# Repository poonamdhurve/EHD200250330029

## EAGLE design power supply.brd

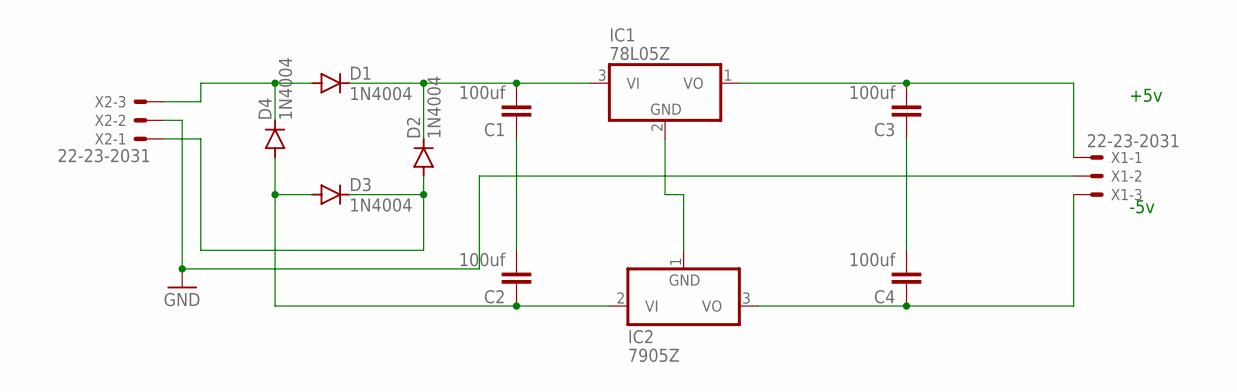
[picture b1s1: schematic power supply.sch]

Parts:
C1, C2, C3, C4: 100uf; C2.5-3
D1, D2, D3, D4: 1N4004; DO41-10
IC1: 78L05Z; TO92
IC2: 7905Z; TO92
X1, X2: 22-23-2031

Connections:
GND: X1.2, X2.2
unnamed: D1.A, D4.C, X2.3
unnamed: C2.1, D3.A, D4.A, IC2.2 (VI)
unnamed: D2.A, D3.C, X2.1
unnamed: C1.2, D1.C, D2.C, IC1.3 (VI)
unnamed: IC1.2 (GND), IC2.1 (GND)
unnamed: C1.1, C2.2
unnamed: C4.1, IC2.3 (VO), X1.3
unnamed: C3.2, IC1.1 (VO), X1.1
unnamed: C3.1, C4.2

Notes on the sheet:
+5v
-5v

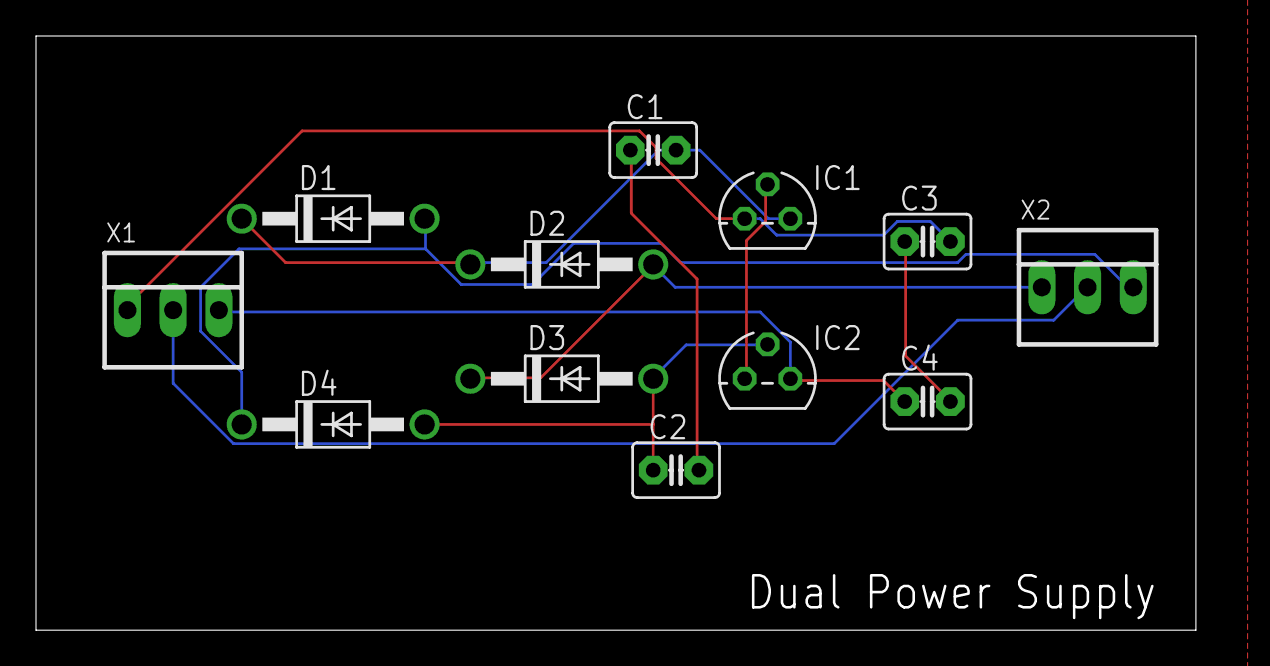
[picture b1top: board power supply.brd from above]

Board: 2 copper layers, 66.6 x 33.0 mm, 12 parts (0 on the bottom side), 10 nets.

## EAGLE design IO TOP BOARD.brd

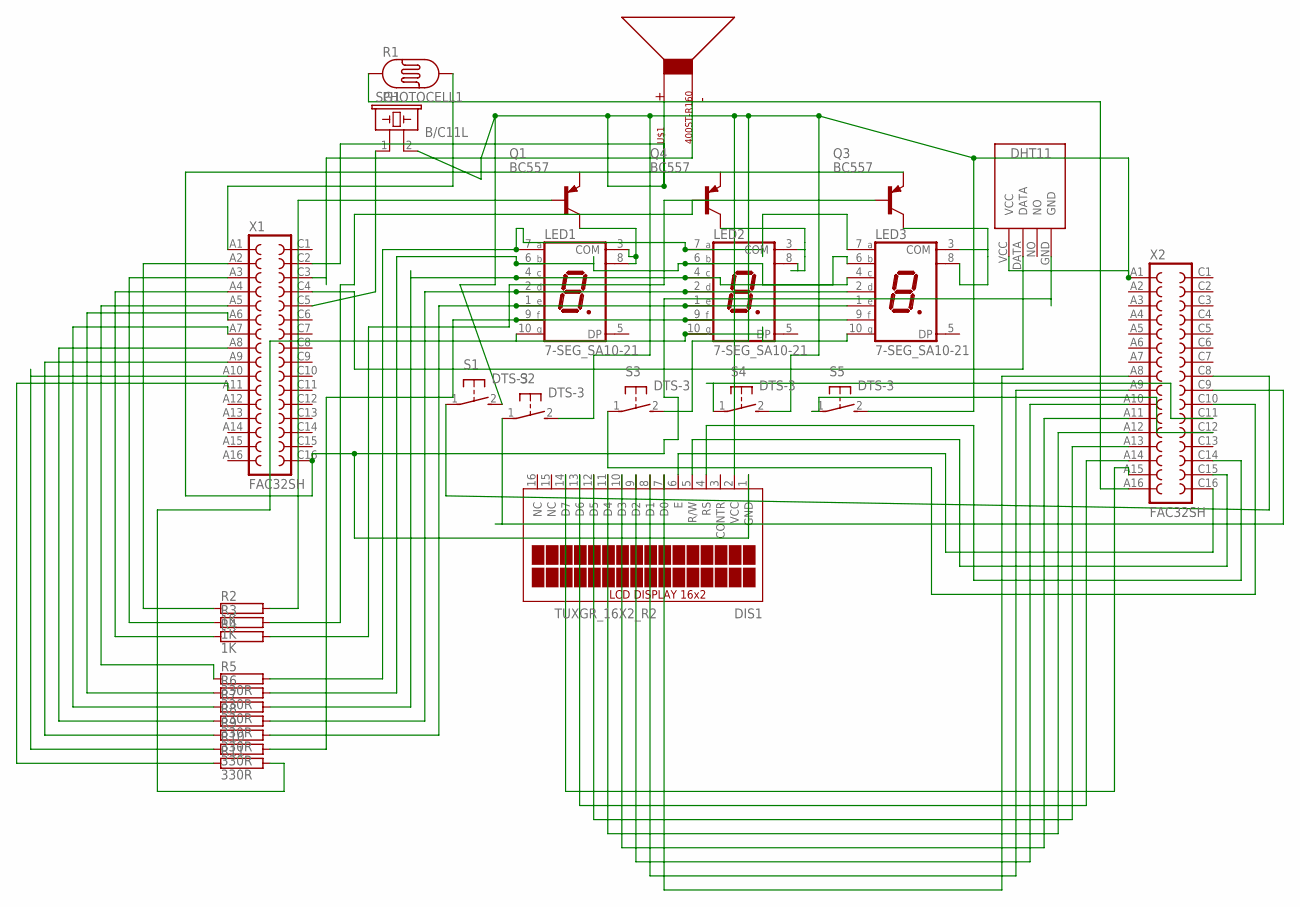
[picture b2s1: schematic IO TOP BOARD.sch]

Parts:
DIS1: TUXGR_16X2_R2
LED1, LED2, LED3: 7-SEG_SA10-21; SA10-21
Q1, Q3, Q4: BC557; TO92
R1: PHOTOCELL1; LDR_OFFBOARD
R2, R3, R4: 1K; TO-247-2H
R5, R6, R7, R8, R9, R10, R11: 330R; TO-247-2H
S1, S2, S3, S4, S5: DTS-3
SG1: B/C11L
U$1: 400ST-R160; 400STR160
U$2: DHT11
X1, X2: FAC32SH

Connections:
unnamed: LED1.3 (COM), LED1.8 (COM), Q1.3 (C)
unnamed: U$1.P$2, X1.C3
unnamed: U$2.DATA, X1.C4
unnamed: SG1.1, X1.C5
unnamed: DIS1.6 (E), X2.C16
unnamed: DIS1.5 (R/W), X2.C15
unnamed: DIS1.4 (RS), X2.C14
unnamed: R1.1, X2.A16
unnamed: DIS1.7 (D0), X2.A8
unnamed: DIS1.8 (D1), X2.A9
unnamed: DIS1.9 (D2), X2.A10
unnamed: DIS1.10 (D3), X2.A11
unnamed: DIS1.11 (D4), X2.A12
unnamed: DIS1.12 (D5), X2.A13
unnamed: DIS1.13 (D6), X2.A14
unnamed: DIS1.14 (D7), X2.A15
unnamed: S1.1, X2.C8
unnamed: S2.1, X2.C9
unnamed: S3.1, X2.C10
unnamed: S4.1, X2.C11
unnamed: S5.1, X2.C12
unnamed: DIS1.2 (VCC), S1.2, S2.2, S3.2, S4.2, S5.2, SG1.2, U$1.P$1, U$2.VCC, X1.C2, X2.A1
unnamed: DIS1.1 (GND), Q3.1 (E), U$2.GND, X1.C16
unnamed: R1.2, X1.A1
unnamed: LED2.3 (COM), LED2.8 (COM), Q4.3 (C)
unnamed: LED3.3 (COM), LED3.8 (COM), Q3.3 (C)
unnamed: Q1.2 (B), R2.2
unnamed: Q4.2 (B), R3.2
unnamed: Q3.2 (B), R4.2
unnamed: LED1.7 (A), LED2.7 (A), LED3.7 (A), R5.2
unnamed: LED1.6 (B), LED2.6 (B), LED3.6 (B), R6.2
unnamed: LED1.4 (C), LED2.4 (C), LED3.4 (C), R7.2
unnamed: LED1.2 (D), LED2.2 (D), LED3.2 (D), R8.2
unnamed: LED1.1 (E), LED2.1 (E), LED3.1 (E), R9.2
unnamed: LED1.9 (F), LED2.9 (F), LED3.9 (F), R10.2
unnamed: R5.1, X1.A5
unnamed: R2.1, X1.A2
unnamed: R3.1, X1.A3
unnamed: R4.1, X1.A4
unnamed: LED1.10 (G), LED2.10 (G), LED3.10 (G), R11.2
unnamed: R6.1, X1.A6
unnamed: R7.1, X1.A7
unnamed: R8.1, X1.A8
unnamed: R9.1, X1.A9
unnamed: R10.1, X1.A10
unnamed: R11.1, X1.A11

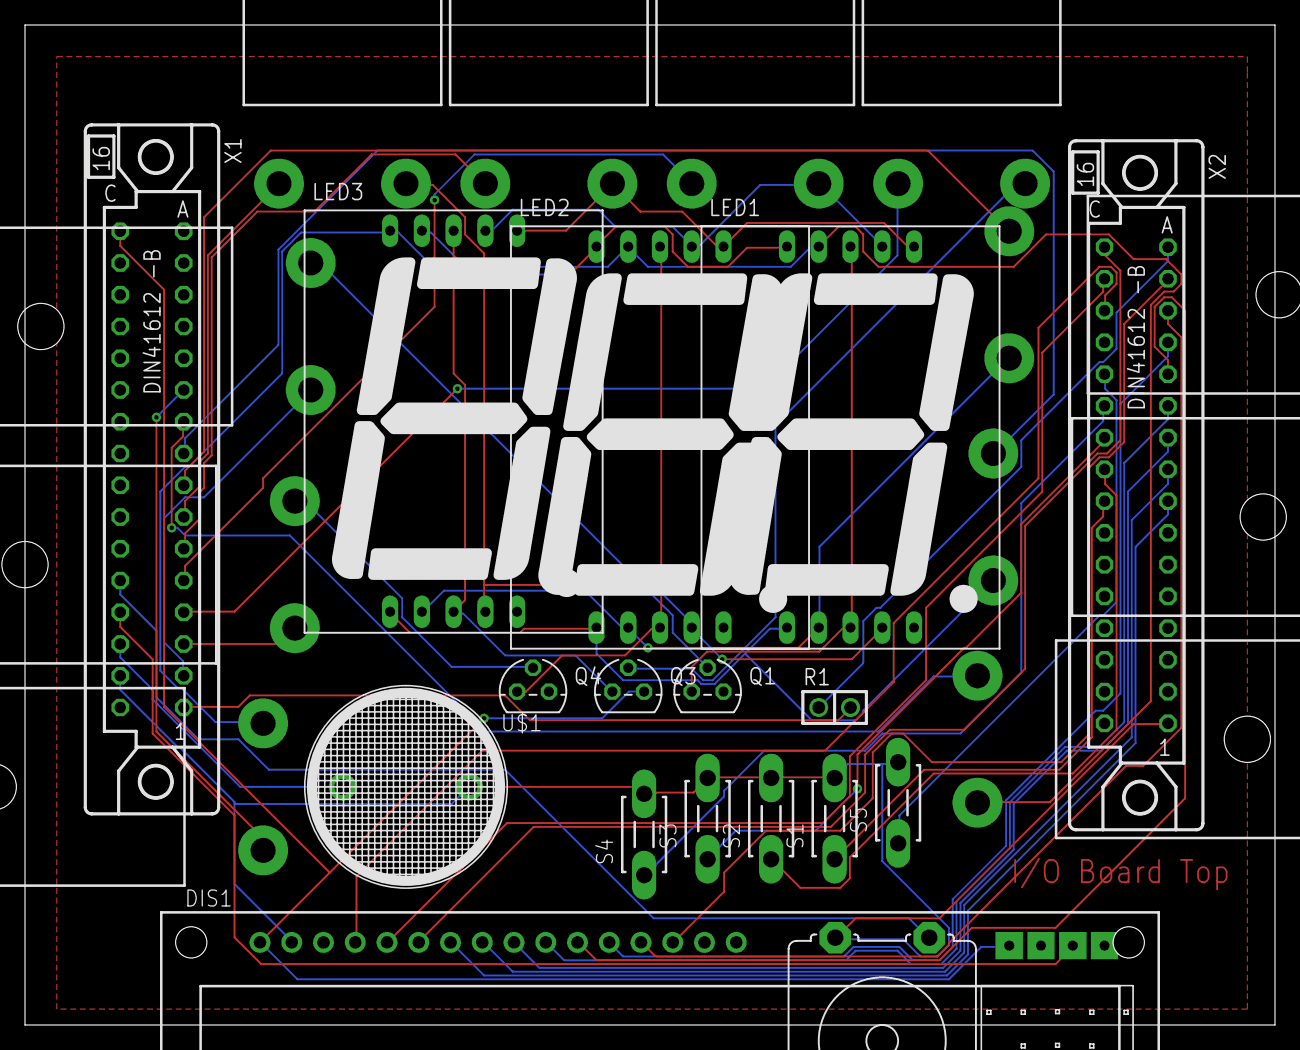
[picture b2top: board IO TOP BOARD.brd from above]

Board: 2 copper layers, 100.0 x 80.0 mm, 28 parts (0 on the bottom side), 46 nets.

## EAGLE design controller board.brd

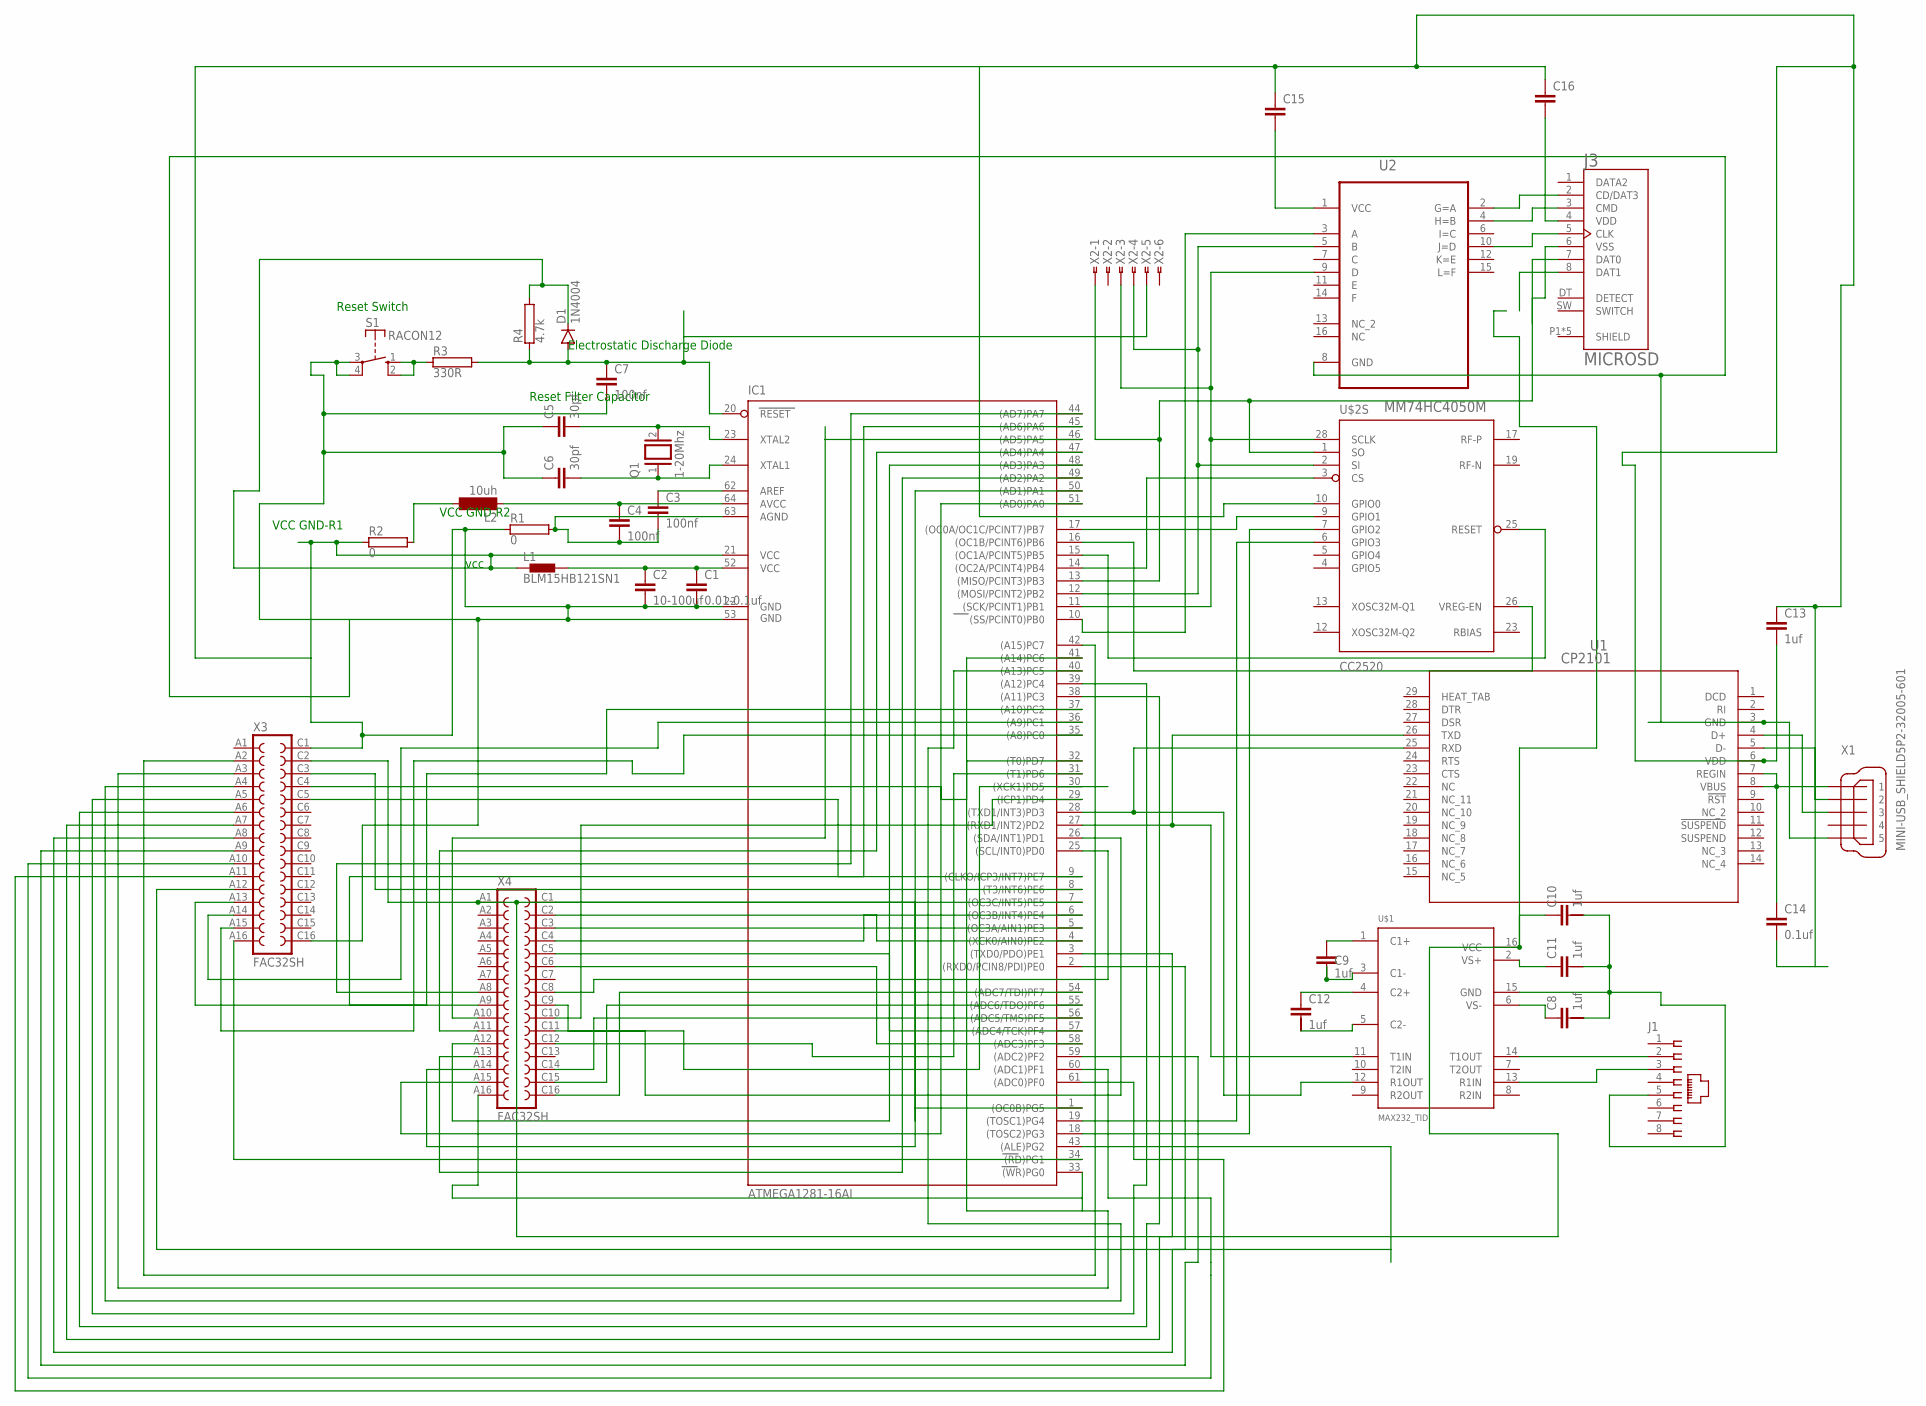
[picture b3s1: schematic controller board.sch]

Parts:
C1: 0.01-0.1uf; C2.5-3
C2: 10-100uf; C2.5-3
C3, C4, C7: 100nf; C2.5-3
C5, C6: 30pf; C2.5-3
C8, C9, C10, C11, C12: 1uf; C2.5/5-2
C13: 1uf; C2.5-3
C14: 0.1uf; C2.5-3
C15, C16: C2,5-3; C2.5-3
D1: 1N4004; DO41-10
IC1: ATMEGA1281-16AI; TQFP64
J1: 555248-1
J3: MICROSD; MOLEX_503182-1852
L1: BLM15HB121SN1; 0402
L2: 10uh; BS11
Q1: 1-20Mhz; Q
R1, R2: 0; TO-247-2H
R3: 330R; TO-247-2H
R4: 4.7k; TO-247-2H
S1: RACON12
U1: CP2101; MLP28_SIL
U2: MM74HC4050M; SOIC127P600X175-16N
U$1: MAX232_TID; R-PDSO-G16
U$2: CC2520; QFN50P500X500X100-29N
X1: MINI-USB_SHIELD5P2-32005-601; 32005-601
X2: FSIDE-6
X3, X4: FAC32SH

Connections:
AGND: U$2.29 (AGND)
AVDD: U$2.11 (AVDD), U$2.14 (AVDD), U$2.16 (AVDD), U$2.20 (AVDD), U$2.22 (AVDD)
AVDD-GUARD: U$2.24 (AVDD-GUARD)
DCOUPL: U$2.27 (DCOUPL)
DVDD: U$2.8 (DVDD)
unnamed: C1.1, C2.1, IC1.52 (VCC1), L1.2
unnamed: C5.2, IC1.23 (XTAL2), Q1.2
unnamed: C3.1, IC1.62 (AREF)
unnamed: C4.1, IC1.64 (AVCC), L2.1
unnamed: C3.2, C4.2, IC1.63 (AGND), R1.2
unnamed: L2.2, R2.2
unnamed: C9.2, C9.3, U$1.3 (C1-)
unnamed: C6.2, IC1.24 (XTAL1), Q1.1
unnamed: R3.1, S1.1 (S), S1.2 (S)
unnamed: C7.1, D1.A, IC1.20 (RESET), R3.2, R4.1, X2.5
unnamed: IC1.34 ((RD)PG1), X3.A16
unnamed: C9.1, U$1.1 (C1+)
unnamed: C12.1, U$1.4 (C2+)
unnamed: C12.2, U$1.5 (C2-)
unnamed: C11.1, U$1.2 (VS+)
unnamed: C8.1, U$1.6 (VS-)
unnamed: C8.2, C10.2, C11.2, J1.5, U$1.15 (GND)
unnamed: IC1.28 ((TXD1/INT3)PD3), U1.25 (RXD), U$1.12 (R1OUT)
unnamed: IC1.27 ((RXD1/INT2)PD2), U1.26 (TXD), U$1.11 (T1IN)
unnamed: U1.4 (D+), X1.3
unnamed: U1.5 (D-), X1.2
unnamed: C14.1, U1.7 (REGIN), U1.8 (VBUS), X1.1
unnamed: C1.2, C2.2, C5.1, C6.1, C7.2, C13.1, C13.2, C14.2, C15.1, C16.1, D1.C, IC1.21 (VCC), IC1.22 (GND), IC1.53 (GND1), L1.1, R1.1, R2.1, R4.2, S1.3, S1.4, U1.3 (GND), U1.6 (VDD), U2.8 (GND), U$2.10 (GPIO0), X1.5, X3.C1, X3.C16
unnamed: J1.2, U$1.14 (T1OUT)
unnamed: J1.3, U$1.13 (R1IN)
unnamed: IC1.18 ((TOSC2)PG3), U$2.7 (GPIO2)
unnamed: IC1.19 ((TOSC1)PG4), U$2.6 (GPIO3)
unnamed: IC1.11 ((SCK/PCINT1)PB1), U2.9 (D), U$2.28 (SCLK), X2.3
unnamed: C15.2, U2.1 (VCC)
unnamed: IC1.10 ((SS/PCINT0)PB0), U2.3 (A)
unnamed: IC1.12 ((MOSI/PCINT2)PB2), U2.5 (B), U$2.2 (SI), X2.4
unnamed: J3.2 (CD/DAT3), U2.2 (G=A)
unnamed: J3.3 (CMD), U2.4 (H=B)
unnamed: J3.5 (CLK), U2.10 (J=D)
unnamed: IC1.13 ((MISO/PCINT3)PB3), J3.7 (DAT0), U$2.1 (SO), X2.1
unnamed: IC1.15 ((OC1A/PCINT5)PB5), U$2.25 (RESET)
unnamed: C16.2, J3.4 (VDD)
unnamed: IC1.16 ((OC1B/PCINT6)PB6), U$2.26 (VREG-EN)
unnamed: IC1.14 ((OC2A/PCINT4)PB4), U$2.3 (CS)
unnamed: IC1.17 ((OC0A/OC1C/PCINT7)PB7), U$2.9 (GPIO1)
unnamed: IC1.35 ((A8)PC0), X3.A15
unnamed: IC1.36 ((A9)PC1), X3.A14
unnamed: IC1.37 ((A10)PC2), X3.A13
unnamed: IC1.1 ((OC0B)PG5), X4.C1
unnamed: IC1.4 ((XCK0/AIN0)PE2), X4.C2
unnamed: IC1.5 ((OC3A/AIN1)PE3), X4.C3
unnamed: IC1.6 ((OC3B/INT4)PE4), X4.C4
unnamed: IC1.57 ((ADC4/TCK)PF4), X4.C5
unnamed: IC1.58 ((ADC3)PF3), X4.C6
unnamed: C10.1, IC1.7 ((OC3C/INT5)PE5), U$1.16 (VCC), X3.C2, X4.A1
unnamed: IC1.8 ((T3/INT6)PE6), X3.C3
unnamed: IC1.32 ((T0)PD7), X3.C4
unnamed: IC1.9 ((CLKO/ICP3/INT7)PE7), X3.C5
unnamed: IC1.54 ((ADC7/TDI)PF7), X4.C16
unnamed: IC1.55 ((ADC6/TDO)PF6), X4.C15
unnamed: IC1.56 ((ADC5/TMS)PF5), X4.C14
unnamed: IC1.44 ((AD7)PA7), X4.A8
unnamed: IC1.45 ((AD6)PA6), X4.A9
unnamed: IC1.46 ((AD5)PA5), X4.A10
unnamed: IC1.47 ((AD4)PA4), X4.A11
unnamed: IC1.48 ((AD3)PA3), X4.A12
unnamed: IC1.49 ((AD2)PA2), X4.A13
unnamed: IC1.50 ((AD1)PA1), X4.A14
unnamed: IC1.51 ((AD0)PA0), X4.A15
unnamed: IC1.33 ((WR)PG0), X4.A16
unnamed: IC1.25 ((SCL/INT0)PD0), X4.C8
unnamed: IC1.26 ((SDA/INT1)PD1), X4.C9
unnamed: IC1.29 ((ICP1)PD4), X4.C10
unnamed: IC1.30 ((XCK1)PD5), X4.C11
unnamed: IC1.31 ((T1)PD6), X4.C12
unnamed: IC1.42 ((A15)PC7), X3.A2
unnamed: IC1.41 ((A14)PC6), X3.A3
unnamed: IC1.40 ((A13)PC5), X3.A4
unnamed: IC1.39 ((A12)PC4), X3.A5
unnamed: IC1.38 ((A11)PC3), X3.A6
unnamed: IC1.3 ((TXD0/PDO)PE1), X3.A7
unnamed: IC1.2 ((RXD0/PCIN8/PDI)PE0), X3.A8
unnamed: IC1.59 ((ADC2)PF2), X3.A9
unnamed: IC1.60 ((ADC1)PF1), X3.A10
unnamed: IC1.61 ((ADC0)PF0), X3.A11
unnamed: IC1.43 ((ALE)PG2), X3.A12

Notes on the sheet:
vcc
VCC GND-R1
VCC GND-R2
Reset Switch
Electrostatic Discharge Diode
Reset Filter Capacitor

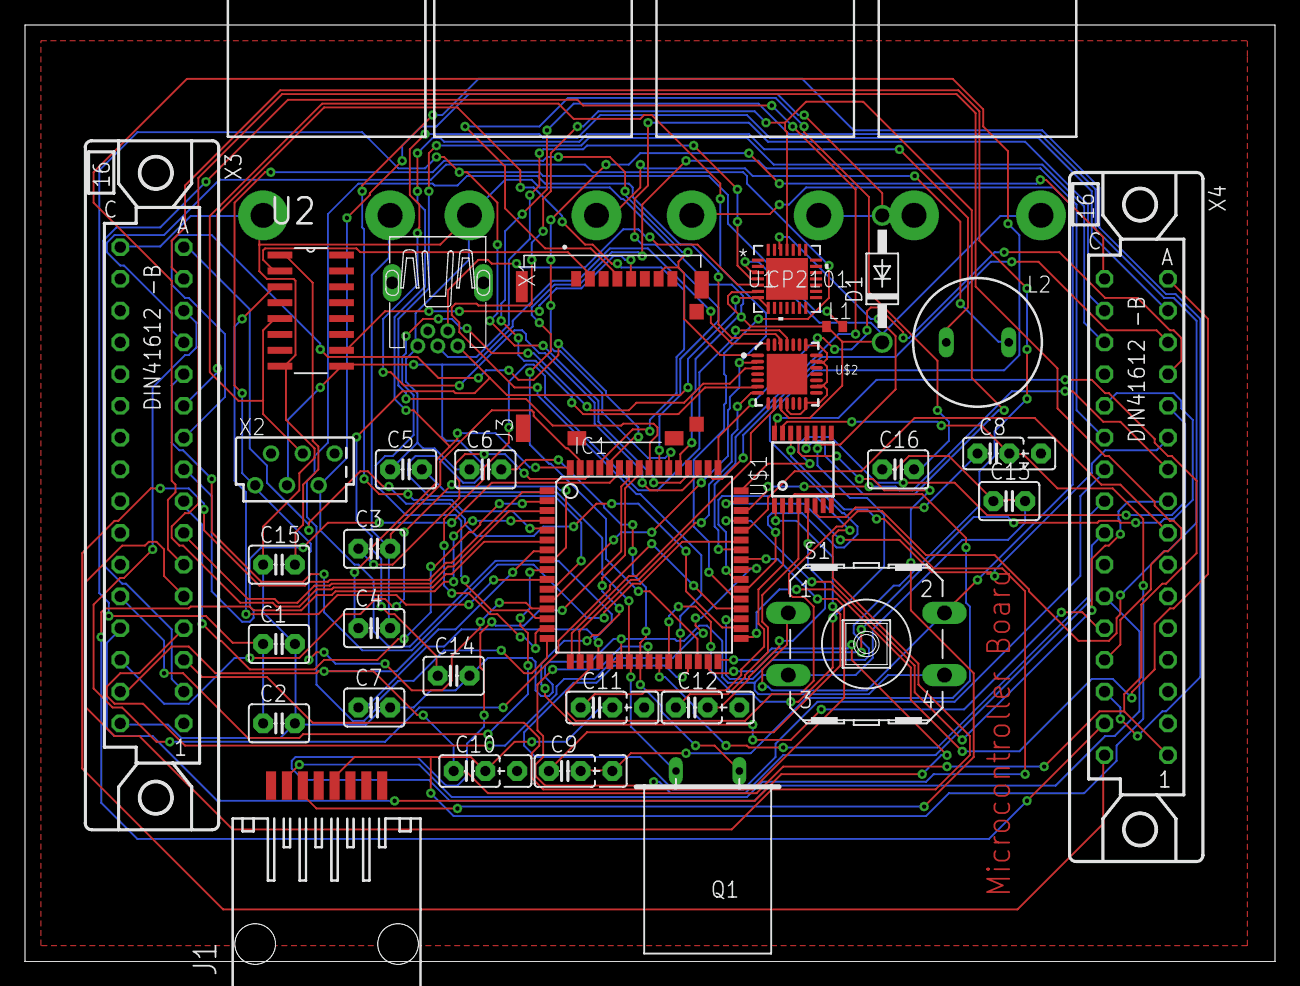
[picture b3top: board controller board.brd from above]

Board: 2 copper layers, 100.0 x 74.9 mm, 36 parts (0 on the bottom side), 82 nets.

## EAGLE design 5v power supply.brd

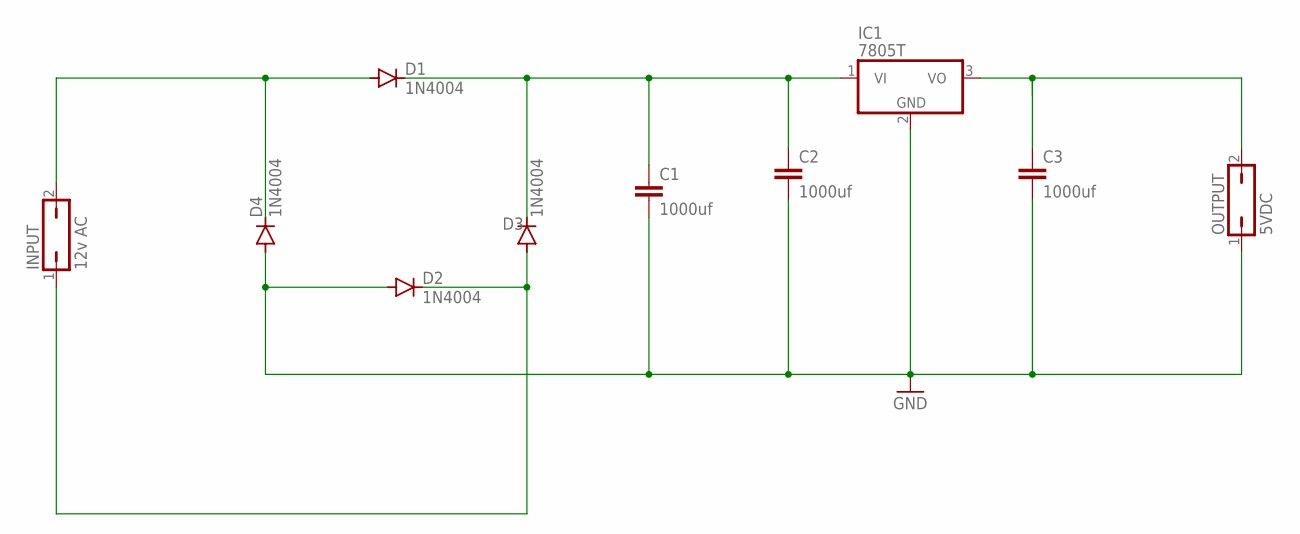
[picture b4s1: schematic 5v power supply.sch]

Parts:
C1, C2, C3: 1000uf; C2.5-3
D1, D2, D3, D4: 1N4004; DO41-10
IC1: 7805T; TO220H
INPUT: 12v AC; JP1
OUTPUT: 5VDC; JP1

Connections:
GND: C1.2, C2.2, C3.2, D2.A, D4.A, IC1.2 (GND), OUTPUT.1
unnamed: D1.A, D4.C, INPUT.2
unnamed: C1.1, C2.1, D1.C, D3.C, IC1.1 (VI)
unnamed: C3.1, IC1.3 (VO), OUTPUT.2
unnamed: D2.C, D3.A, INPUT.1

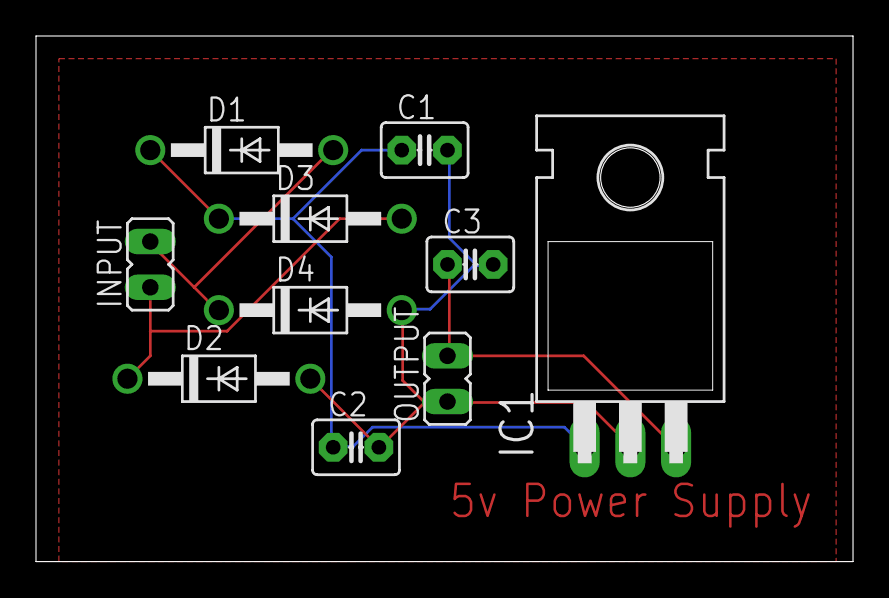
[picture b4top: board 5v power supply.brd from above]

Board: 2 copper layers, 45.4 x 29.2 mm, 10 parts (0 on the bottom side), 5 nets.

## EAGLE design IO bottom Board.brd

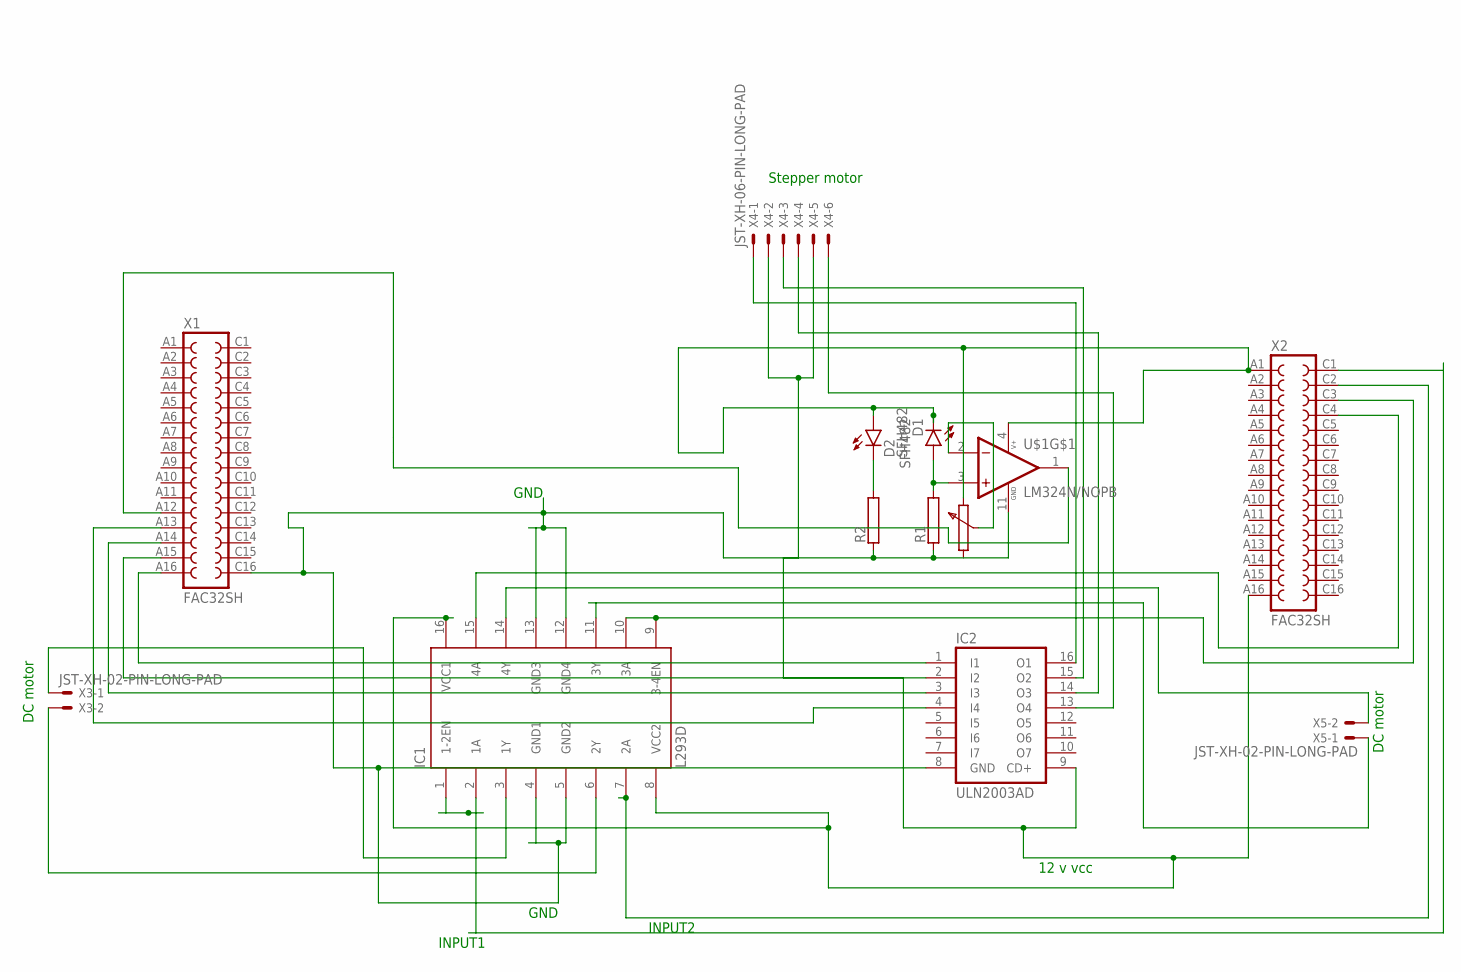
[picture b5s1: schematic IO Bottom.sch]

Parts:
D1, D2: SFH482
IC1: L293D; DIL16
IC2: ULN2003AD; SO16
R1, R2: RMG100-H; TO-247-2H
U$1: LM324N/NOPB; DIP825W47P254L1917H533Q14
X1, X2: FAC32SH
X3, X5: JST-XH-02-PIN-LONG-PAD; JST-XH-02-PACKAGE-LONG-PAD
X4: JST-XH-06-PIN-LONG-PAD; JST-XH-06-PACKAGE-LONG-PAD

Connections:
unnamed: IC1.3 (1Y), X3.1
unnamed: IC1.6 (2Y), X3.2
unnamed: IC1.14 (4Y), X5.2
unnamed: IC1.11 (3Y), X5.1
unnamed: IC1.2 (1A), X2.C1
unnamed: D2.K (C), R2.2
unnamed: IC1.7 (2A), X2.C2
unnamed: D1.A, R1.2, U$1.3 (1IN+)
unnamed: IC2.16 (O1), X4.1
unnamed: IC2.15 (O2), X4.3
unnamed: IC2.14 (O3), X4.4
unnamed: IC2.13 (O4), X4.6
unnamed: U$1.1 (1OUT), X1.A12
unnamed: IC1.4 (GND1), IC1.5 (GND2), IC1.12 (GND4), IC1.13 (GND3), IC2.8 (GND), R1.1, R2.1, U$1.11 (GND), X1.C16
unnamed: IC2.1 (I1), X1.A16
unnamed: IC2.2 (I2), X1.A15
unnamed: IC2.3 (I3), X1.A14
unnamed: IC2.4 (I4), X1.A13
unnamed: IC1.9 (3-4EN), IC1.10 (3A), X2.C3
unnamed: IC1.15 (4A), X2.C4
unnamed: IC1.8 (VCC2), IC1.16 (VCC1), IC2.9 (CD+), X2.A16, X4.2, X4.5
unnamed: D1.K (C), D2.A, U$1.4 (V+), X2.A1

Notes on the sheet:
GND
INPUT1
INPUT2
Stepper motor
DC motor
12 v vcc

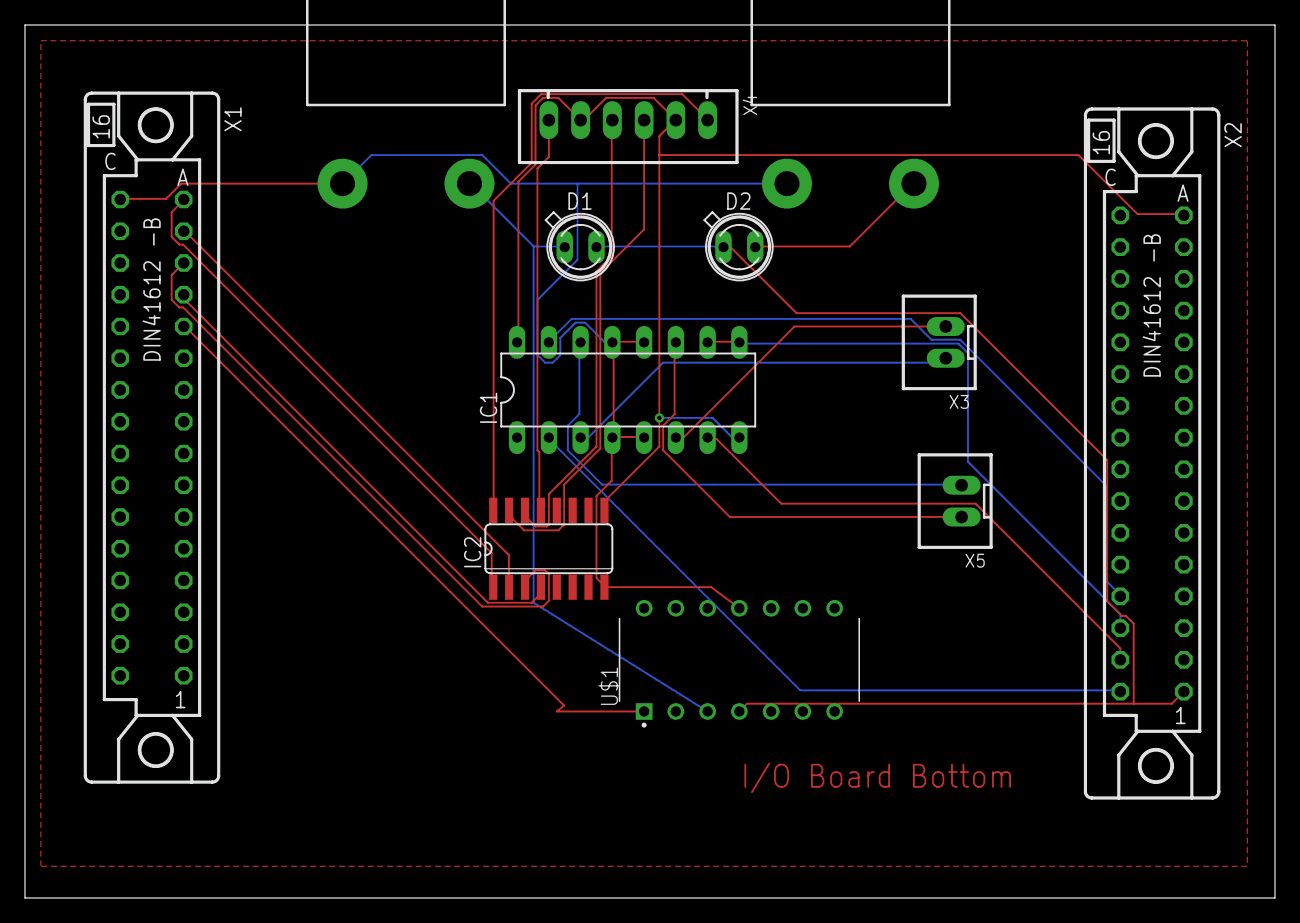
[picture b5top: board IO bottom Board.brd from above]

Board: 2 copper layers, 100.0 x 69.8 mm, 12 parts (0 on the bottom side), 22 nets.
